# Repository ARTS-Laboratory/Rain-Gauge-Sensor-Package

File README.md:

# Rain-Gauge-Sensor-Package
Measuring the rain

<p align="center">
Figure 1: Water drops through the contacters.
</p>

<p align="center">
Figure 2: Testing water drop measurments in (Saif 2021).
</p>

<p align="center">
Figure 3: Prototype hardware.
</p>

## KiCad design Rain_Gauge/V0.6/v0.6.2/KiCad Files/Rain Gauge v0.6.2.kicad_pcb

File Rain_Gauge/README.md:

# UAV deployable Raingauge

## V0.1 Keith's background work

## V0.2 Keith's drop conductivity gauge

## V0.3 Saif's drop conductivity gauge

## V0.4 Ava's drop conductivity gauge

## V0.5 Ryan Brown's drop conductivity gauge

## V0.6 Chris's drop conductivity gauge

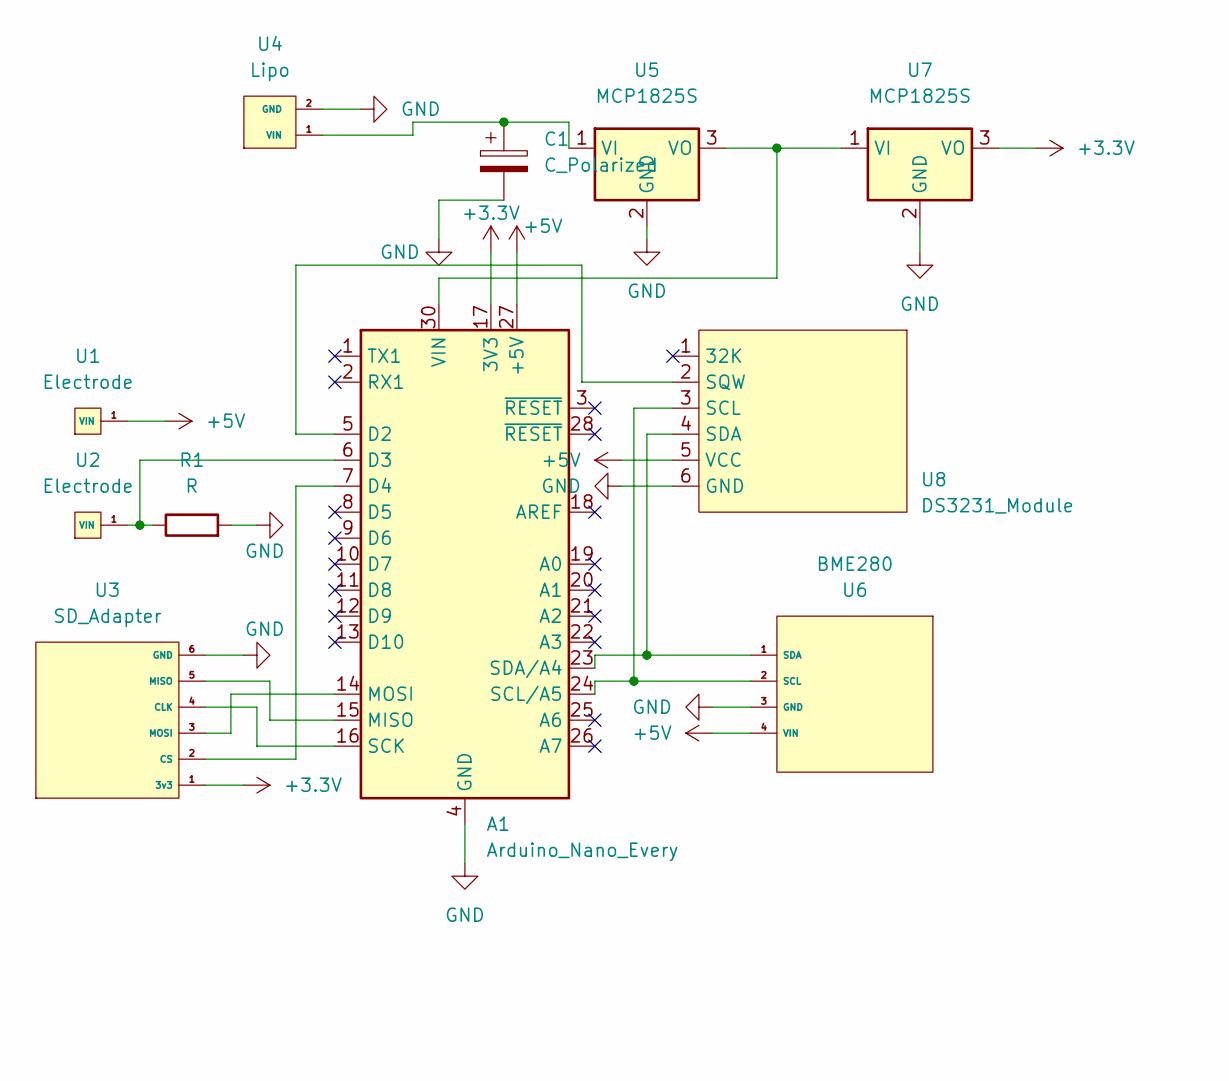
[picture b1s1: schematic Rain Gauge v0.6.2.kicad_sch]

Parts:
A1: Arduino_Nano_Every; Arduino_Nano
C1: C_Polarized; C_1206_3216Metric
R1: R; R_1206_3216Metric
U1, U2: Electrode
U3: SD_Adapter; 3.3v SD Adapter
U4: Lipo
U5, U7: MCP1825S; SOT230P700X180-4N
U6: BME280
U8: DS3231_Module; 3.3v SD Adapter

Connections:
+3V3: A1.17 (3V3), U3.1 (3v3), U7.3 (VO)
+5V: A1.27 (+5V), U1.1 (VIN), U6.4 (VIN), U8.5 (VCC)
GND: A1.4 (GND), A1.29 (GND), C1.2, R1.2, U3.6 (GND), U4.2 (GND), U5.2 (GND), U6.3 (GND), U7.2 (GND), U8.6 (GND)
unnamed: A1.5 (D2), U8.2 (SQW)
unnamed: A1.6 (D3), R1.1, U2.1 (VIN)
unnamed: A1.7 (D4), U3.2 (CS)
unnamed: A1.14 (MOSI), U3.3 (MOSI)
unnamed: A1.15 (MISO), U3.5 (MISO)
unnamed: A1.16 (SCK), U3.4 (CLK)
unnamed: A1.23 (SDA/A4), U6.1 (SDA), U8.4 (SDA)
unnamed: A1.24 (SCL/A5), U6.2 (SCL), U8.3 (SCL)
unnamed: A1.30 (VIN), U5.3 (VO), U7.1 (VI)
unnamed: C1.1, U4.1 (VIN), U5.1 (VI)

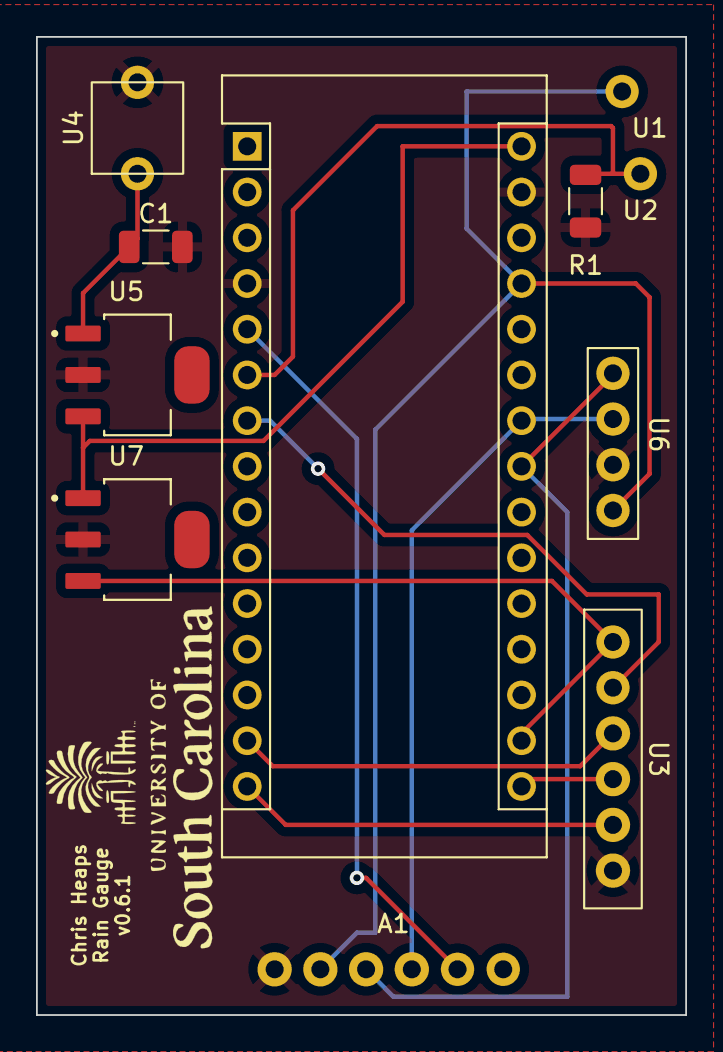
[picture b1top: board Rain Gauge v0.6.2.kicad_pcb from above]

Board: 2 copper layers, 36.1 x 54.3 mm, 11 parts (1 on the bottom side), 13 nets.

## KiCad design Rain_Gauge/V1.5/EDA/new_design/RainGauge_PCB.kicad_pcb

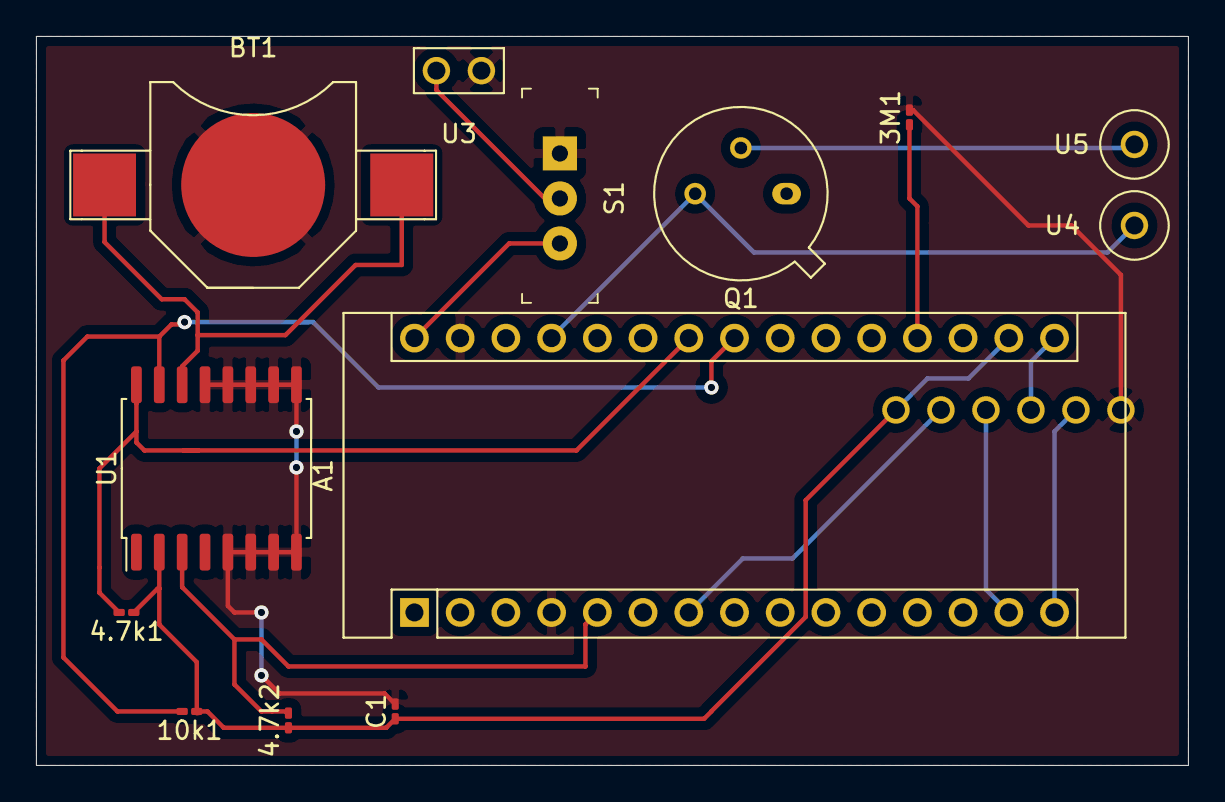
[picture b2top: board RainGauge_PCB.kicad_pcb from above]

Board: 2 copper layers, 64.0 x 40.5 mm, 14 parts (1 on the bottom side), 15 nets.

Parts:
3M1, 4.7k1, 4.7k2, 10k1: R; R_0201_0603Metric_Pad0.64x0.40mm_HandSolder
A1: Arduino_Nano_v3.x; Arduino_Nano
BT1: Battery; battery_holder_10mm
C1: C; C_0201_0603Metric_Pad0.64x0.40mm_HandSolder
Q1: 2N2219; TO-39-3
S1: EG1218; Switch_Slide_11.6x4mm_EG1218
U1: DS3231M; SOIC-16W_7.5x10.3mm_P1.27mm
U2: SD_Card; SD_card
U3: Battery_Leads; battery_leads
U4, U5: Electrode_TH; electrode

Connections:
GND: 3M1.2, A1.4, A1.29, BT1.2, C1.2, S1.1, U1.5, U1.6, U1.7, U1.8, U1.9, U1.10, U1.11, U1.12, U1.13, U2.1, U3.2
unnamed: 3M1.1, A1.19
unnamed: 4.7k1.2, A1.24, U1.16
unnamed: 4.7k2.2, A1.5, U1.3
unnamed: 4.7k1.1, 4.7k2.1, 10k1.1, A1.17, C1.1, U1.2, U2.6
unnamed: 10k1.2, A1.23, U1.15
unnamed: A1.7, U2.5
unnamed: A1.14, U2.4
unnamed: A1.15, U2.2
unnamed: A1.16, U2.3
unnamed: A1.27, Q1.3, U4.1
unnamed: A1.30, S1.3
unnamed: BT1.1, U1.14
unnamed: Q1.2, U5.1
unnamed: S1.2, U3.1

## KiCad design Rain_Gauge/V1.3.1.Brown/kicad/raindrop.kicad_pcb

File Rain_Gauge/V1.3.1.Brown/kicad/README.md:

# Notes

1. Need to add the component library local. Add "Saif_micro_sd" to this folder. 
1. Update basic component list.

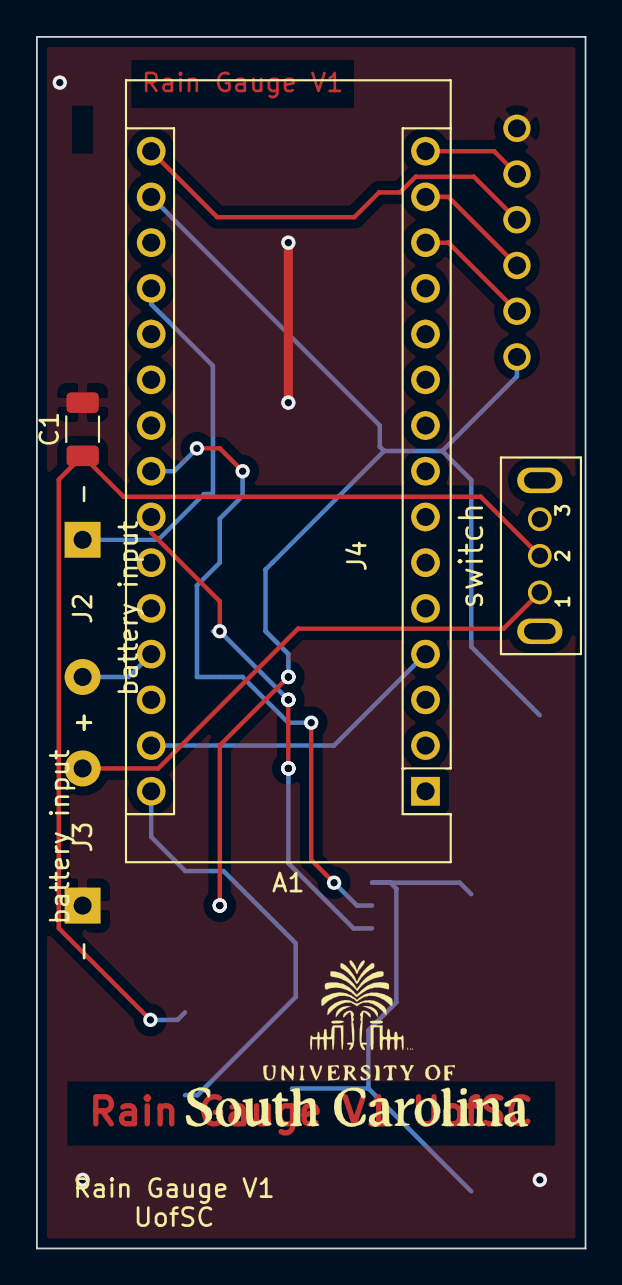
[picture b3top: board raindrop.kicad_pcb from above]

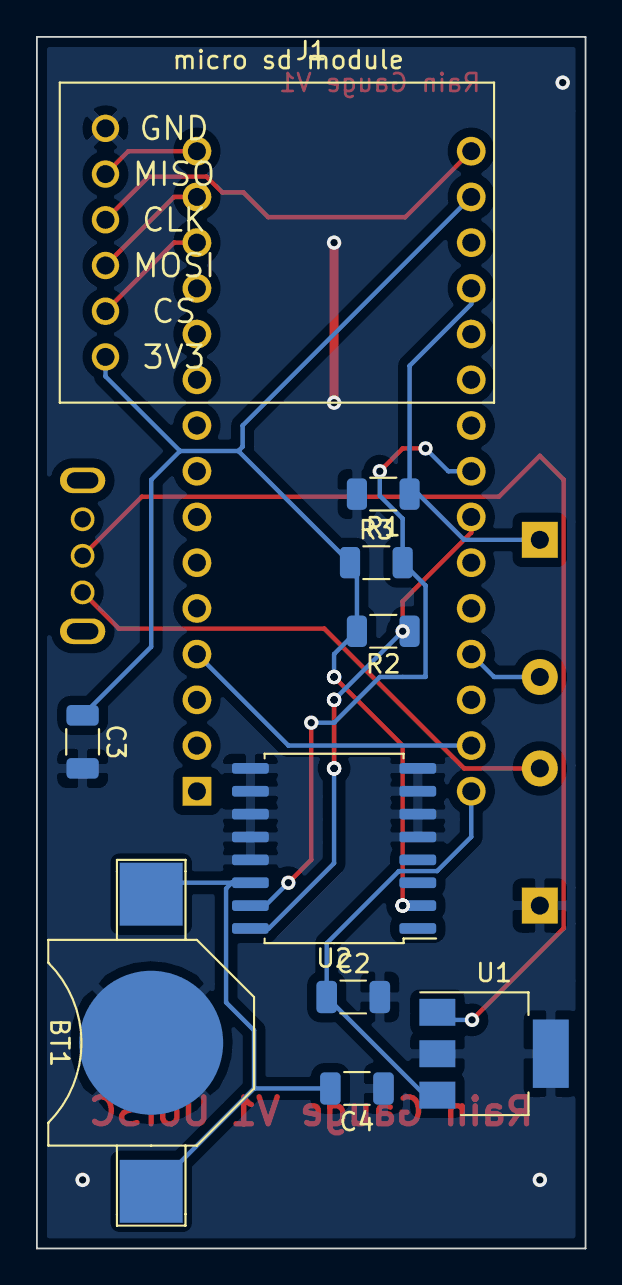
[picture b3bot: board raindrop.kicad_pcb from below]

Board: 2 copper layers, 30.5 x 67.3 mm, 15 parts (10 on the bottom side), 15 nets.

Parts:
A1: Arduino_Nano_v3.x; Arduino_Nano
BT1: Battery_Cell; battery_holder_10mm
C1, C2, C3, C4: C; C_1206_3216Metric
J1: Saif_micro_sd; SD_Module
J2: Screw_Terminal_01x02; Battery_Input
J3: Conn_01x02_Female; Battery_Input
J4: switch; grounded_switch
R1, R2, R3: R; R_1206_3216Metric
U1: L7805; SOT-223-3_TabPin2
U2: DS3231M; SOIC-16W_7.5x10.3mm_P1.27mm

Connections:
Earth: BT1.2, C1.2, C2.2, C3.2, C4.1, J1.6, J3.2, R1.2, U1.2, U2.5, U2.6, U2.7, U2.8, U2.9, U2.10, U2.11, U2.12, U2.13
GND: A1.4, A1.29
unnamed: A1.13, J1.2
unnamed: A1.14, J1.3
unnamed: A1.15, J1.5
unnamed: A1.16, J1.4
unnamed: A1.17, C3.1, J1.1, R2.2, R3.1, U2.2
unnamed: A1.19, J2.2, R1.1
unnamed: A1.23, R3.2, U2.15
unnamed: A1.24, R2.1, U2.16
unnamed: A1.27, J2.1
unnamed: A1.30, C2.1, U1.3
unnamed: BT1.1, C4.2, U2.14
unnamed: C1.1, J4.2, U1.1
unnamed: J3.1, J4.1

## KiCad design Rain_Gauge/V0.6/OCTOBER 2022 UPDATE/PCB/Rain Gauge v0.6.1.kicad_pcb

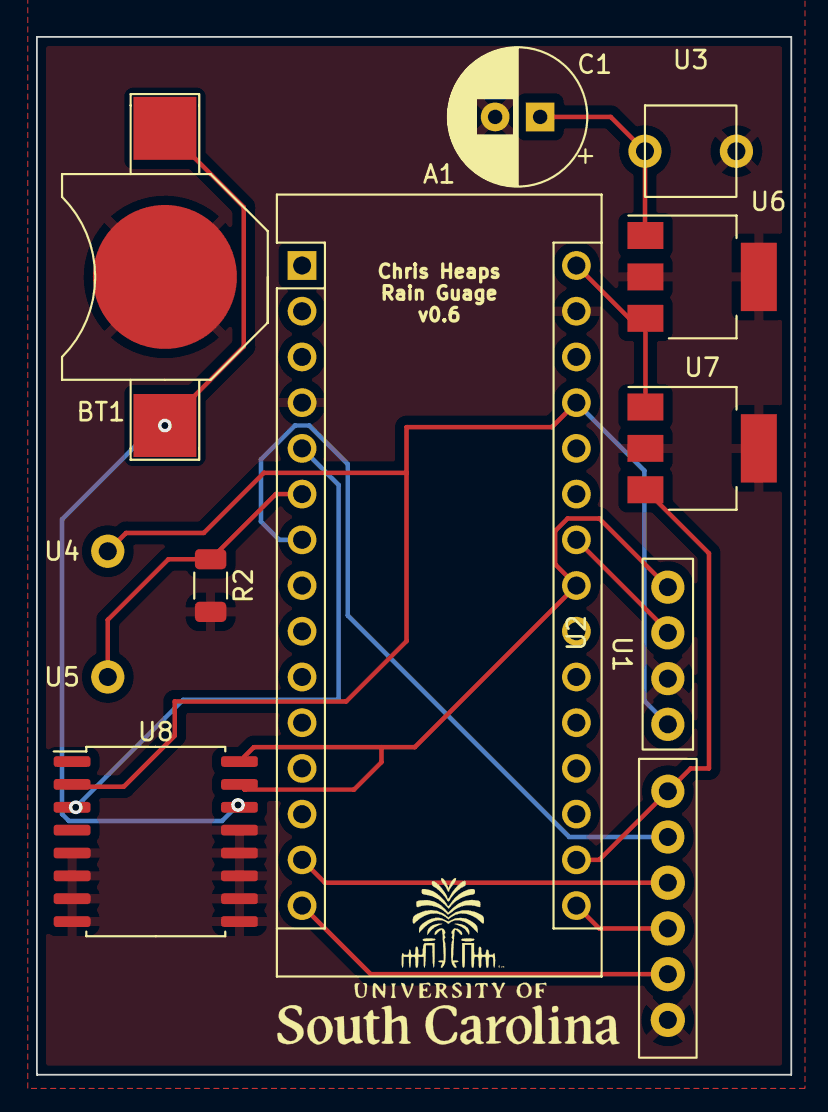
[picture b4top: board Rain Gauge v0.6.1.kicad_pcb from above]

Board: 2 copper layers, 41.9 x 57.7 mm, 12 parts (0 on the bottom side), 14 nets.

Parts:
A1: Arduino_Nano_Every; Arduino_Nano
BT1: Battery_Cell; battery_holder_10mm
C1: C_Polarized; CP_Radial_D7.5mm_P2.50mm
R2: 3M; R_1206_3216Metric
U1: SD_Adapter; 3.3v SD Adapter
U2: BME280
U3: Lipo
U4, U5: Electrode
U6: LM2937xMP; SOT-223-3_TabPin2
U7: MCP1825S; SOT-223-3_TabPin2
U8: DS3231M; SOIC-16W_7.5x10.3mm_P1.27mm

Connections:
+3V3: A1.17 (3V3), U1.1 (3V3), U7.3 (VO)
+5V: A1.27 (+5V), U2.1 (VIN), U4.1 (VIN), U8.2 (VCC)
GND: A1.4 (GND), A1.29 (GND), BT1.2 (-), C1.2, R2.2, U1.6 (GND), U2.2 (GND), U3.2 (GND), U6.2 (GND), U7.2 (GND), U8.5 (GND), U8.6 (GND), U8.7 (GND), U8.8 (GND), U8.9 (GND), U8.10 (GND), U8.11 (GND), U8.12 (GND), U8.13 (GND)
unnamed: A1.5 (D2), U8.3 (~INT/SQW)
unnamed: A1.6 (D3), R2.1, U5.1 (VIN)
unnamed: A1.7 (D4), U1.2 (CS)
unnamed: A1.14 (MOSI), U1.3 (MOSI)
unnamed: A1.15 (MISO), U1.5 (MISO)
unnamed: A1.16 (SCK), U1.4 (CLK)
unnamed: A1.23 (SDA/A4), U2.4 (SDA), U8.15 (SDA), U8.16 (SCL)
unnamed: A1.24 (SCL/A5), U2.3 (SCL)
unnamed: A1.30 (VIN), U6.3 (VO), U7.1 (VI)
unnamed: BT1.1 (+), U8.14 (VBAT)
unnamed: C1.1, U3.1 (VIN), U6.1 (VI)

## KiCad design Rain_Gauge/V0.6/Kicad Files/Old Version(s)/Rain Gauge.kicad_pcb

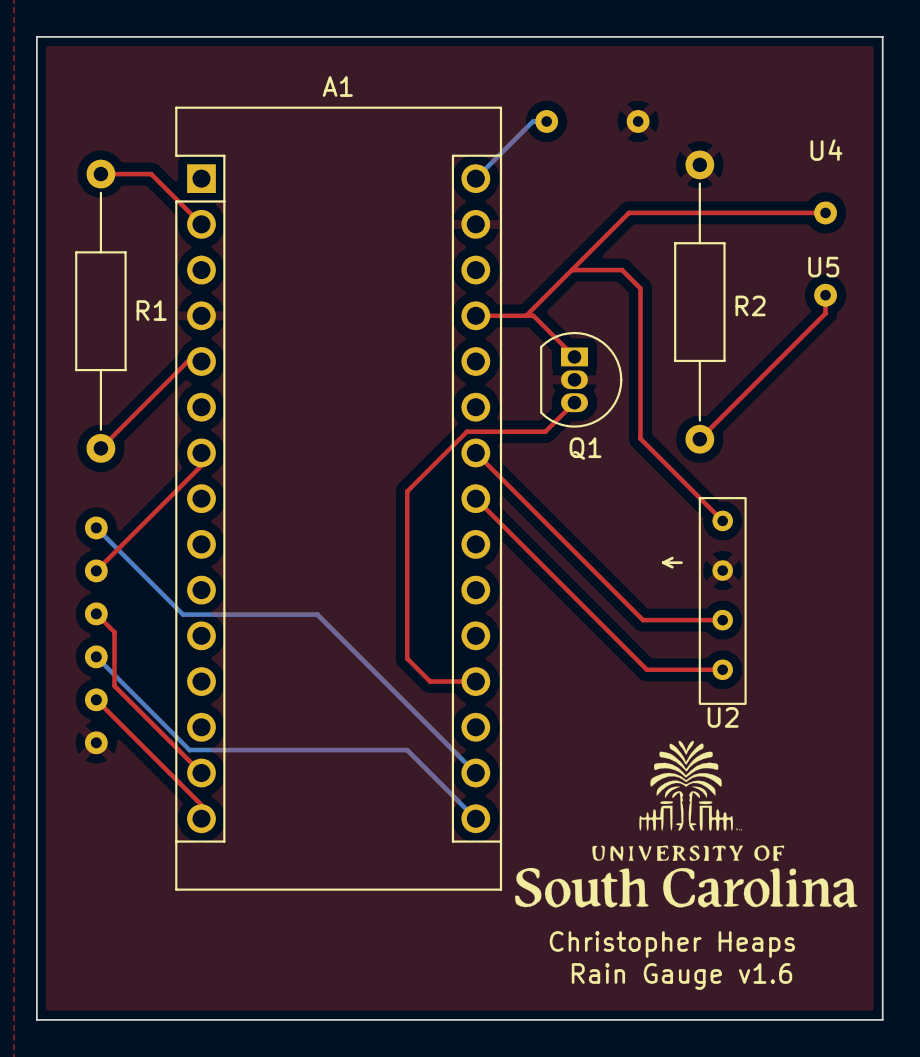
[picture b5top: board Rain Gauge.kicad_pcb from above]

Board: 2 copper layers, 47.0 x 54.6 mm, 9 parts (0 on the bottom side), 14 nets.

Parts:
A1: Arduino_Nano_Every; Arduino_Nano
Q1: PN2222A; TO-92_Inline
R1: 220; R_Axial_DIN0207_L6.3mm_D2.5mm_P15.24mm_Horizontal
R2: 3M; R_Axial_DIN0207_L6.3mm_D2.5mm_P15.24mm_Horizontal
U1: SD_Adapter; 3.3v SD Adapter
U2: BME280
U3: Lipo
U4, U5: Electrode

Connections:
+3V3: A1.17 (3V3), U1.1 (3V3)
+5V: A1.27 (+5V), Q1.1 (E), U2.1 (VIN), U4.1 (VIN)
+BATT: A1.30 (VIN), U3.2 (GND)
GND: A1.4 (GND), A1.29 (GND), Q1.2 (B), R2.1, U1.6 (GND), U2.2 (GND), U3.1 (VIN)
unnamed: A1.2 (RX1), R1.1
unnamed: A1.5 (D2), R1.2
unnamed: A1.7 (D4), U1.2 (CS)
unnamed: A1.14 (MOSI), U1.3 (MOSI)
unnamed: A1.15 (MISO), U1.5 (MISO)
unnamed: A1.16 (SCK), U1.4 (CLK)
unnamed: A1.23 (SDA/A4), U2.4 (SDA)
unnamed: A1.24 (SCL/A5), U2.3 (SCL)
unnamed: A1.19 (A0), Q1.3 (C)
unnamed: R2.2, U5.1 (VIN)

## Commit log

2021-12-09 initial comit
2022-01-31 Create V1.5-Brown
2022-02-02 created new version
2022-02-02 cleaning up file setup
2022-02-02 README files
2022-02-18 these are my changes
2022-02-18 main image
2022-02-18 clean up files
2022-02-18 cleaned up Ryan's files
2022-02-18 add ARTS-lab footprints and symbols
2022-02-21 Adding Ava's stuff
2022-02-24 Reorganize and new PCB
2022-03-02 KiCad Stuff
2022-03-21 housekeeping
2022-04-13 Added pics to front page.
2022-06-10 Added a condition that only lets Arduino work at a certain humidity level-saves power
    This code takes TDS readings at a certain humidity level from a BME280 sensor and saves to a microSD card in Excel format. The Arduino is asleep otherwise to help save power and not take unnecessary 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
2022-06-13 Cap for PVC
    Planning to make the gauge in a pvc pipe with a funnel leading into it- this is just a quick version for prototyping.
2022-06-16 added markdown files for Keith's work
2022-06-16 added a few figs to markdown files
2022-06-17 updated keiths ppt to pdf
2022-06-30 Chris' Work
2022-07-01 added license
2022-07-05 Chris' work
    Adding some photos
2022-07-11 Chris' work
    Sensor housing for rain gauge- has space for PCB and battery.
2022-07-13 Renamed folder versions
2022-09-08 9/8/2022 Update-Chris H.
2022-09-08 9/8/22 Update-Chris H.
2022-10-24 October 2022 Update-Chris H.
2023-03-01 Adding v0.6.1- latest work
2023-05-18 Adding KiCad and Program files
    Adding files for a redesigned PCB that will be used for a working prototype for now- will add 3d print & CAD files soon
2023-05-18 Kicad Files
2023-05-30 Adding code
2023-07-03 Version number updates
2023-07-11 Update to Arduino code
